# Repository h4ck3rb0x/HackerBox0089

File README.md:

# HackerBox0089
Wispy Wardriver

[HackerBox 0089 Product Page](https://hackerboxes.com/products/hackerbox-0089-wispy)

[HackerBox 0089 Official Online Guide](https://www.instructables.com/HackerBox-0089-WiSpy/)

Closely inspired by the [Wardriver.UK](https://wardriver.uk/) project.

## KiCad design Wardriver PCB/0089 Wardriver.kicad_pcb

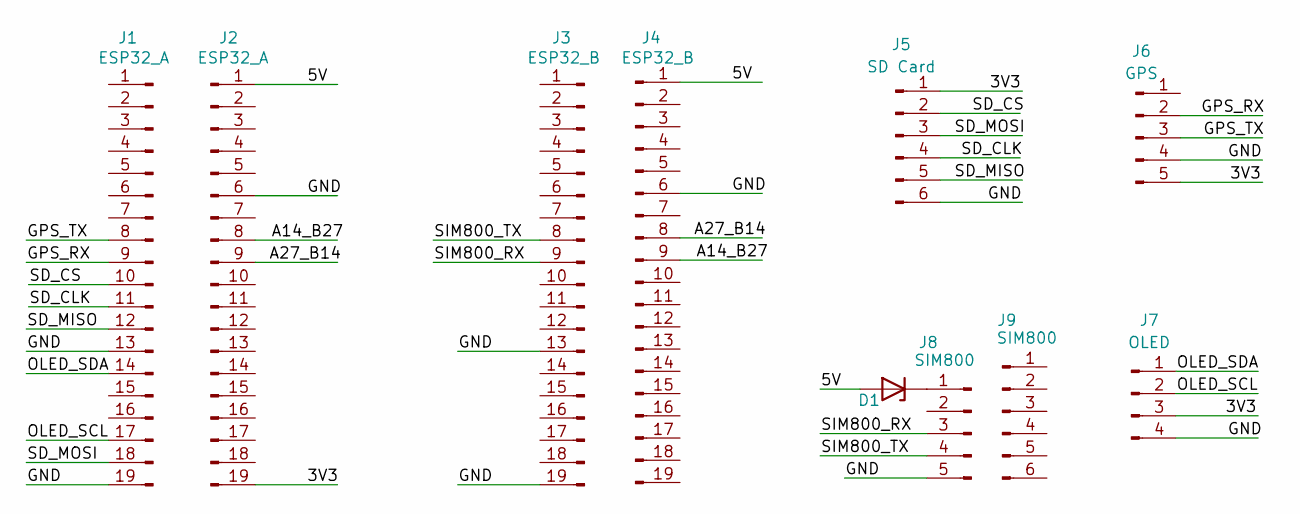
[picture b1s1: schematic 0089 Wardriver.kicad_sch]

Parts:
D1: 85C; D_DO-34_SOD68_P7.62mm_Horizontal
J1, J2: ESP32_A; PinHeader_1x19_P2.54mm_Vertical
J3, J4: ESP32_B; PinHeader_1x19_P2.54mm_Vertical
J5: SD Card; PinHeader_1x06_P2.54mm_Vertical
J6: GPS; PinHeader_1x05_P2.54mm_Vertical
J7: OLED; PinHeader_1x04_P2.54mm_Vertical
J8: SIM800; PinHeader_1x05_P2.54mm_Vertical
J9: SIM800; PinHeader_1x06_P2.54mm_Vertical

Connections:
/3V3: J2.19, J5.1, J6.5, J7.3
/5V: D1.2 (A), J2.1, J4.1
/A14_B27: J2.8, J4.9
/A27_B14: J2.9, J4.8
/GND: J1.13, J1.19, J2.6, J3.13, J3.19, J4.6, J5.6, J6.4, J7.4, J8.5
/GPS_RX: J1.9, J6.2
/GPS_TX: J1.8, J6.3
/OLED_SCL: J1.17, J7.2
/OLED_SDA: J1.14, J7.1
/SD_CLK: J1.11, J5.4
/SD_CS: J1.10, J5.2
/SD_MISO: J1.12, J5.5
/SD_MOSI: J1.18, J5.3
/SIM800_RX: J3.9, J8.3
/SIM800_TX: J3.8, J8.4
unnamed: D1.1 (K), J8.1

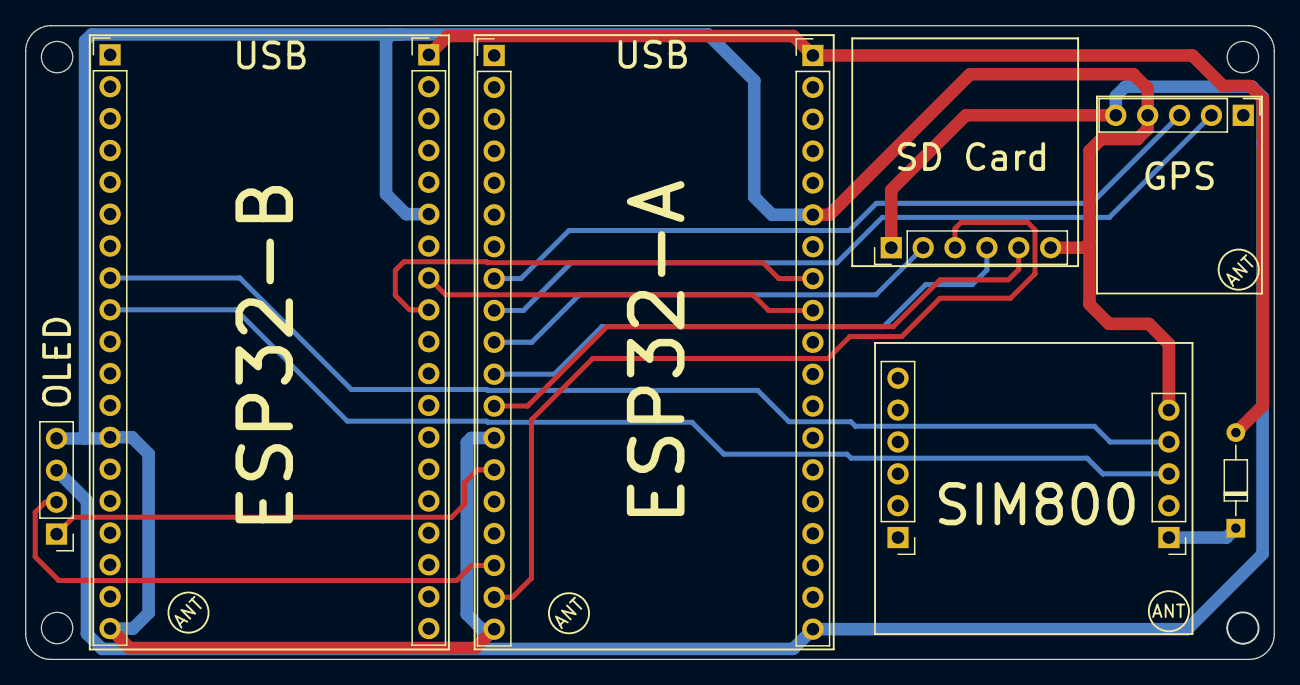
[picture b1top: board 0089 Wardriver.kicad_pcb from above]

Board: 2 copper layers, 99.5 x 50.5 mm, 10 parts (0 on the bottom side), 16 nets.
